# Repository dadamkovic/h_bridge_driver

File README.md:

The project is an implementation of an H-bridge driving IC DRV8702QRHBRQ1 that allows control of full H-bridge motor driver in different modes.
The ECU includes:
- buttons for manual control of the motor in both direction + braking
- Status LED
- ON/OFF switch
- Interface for banana plugs and probes
- Interface for electrical control

A chassis designed for 3D printing that protects the ECU. It is inteded to be printed from 3 pieces:
- 2x hard plastic shell (PLA, ABS, ...)
- 1x soft shell for protection against bumps (TPA)

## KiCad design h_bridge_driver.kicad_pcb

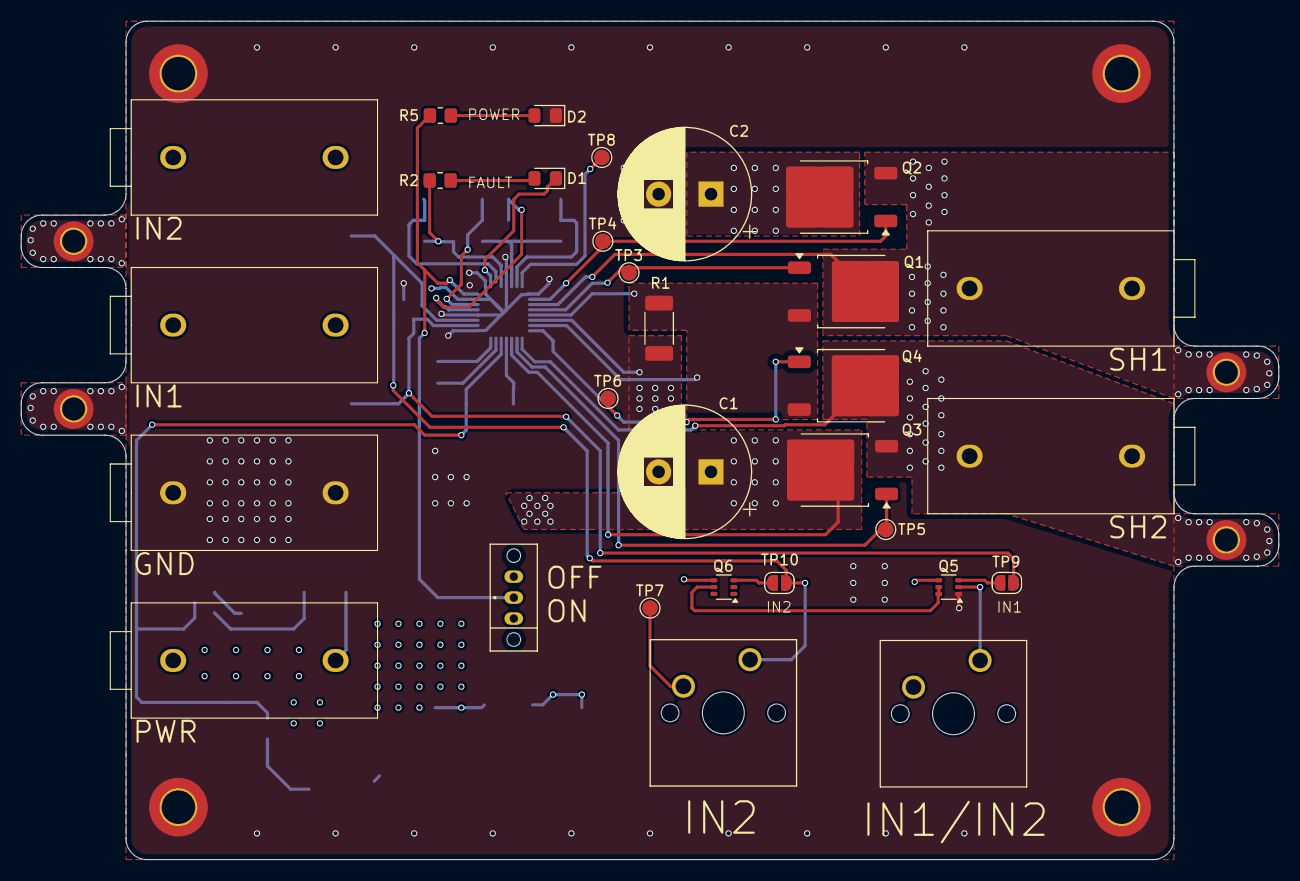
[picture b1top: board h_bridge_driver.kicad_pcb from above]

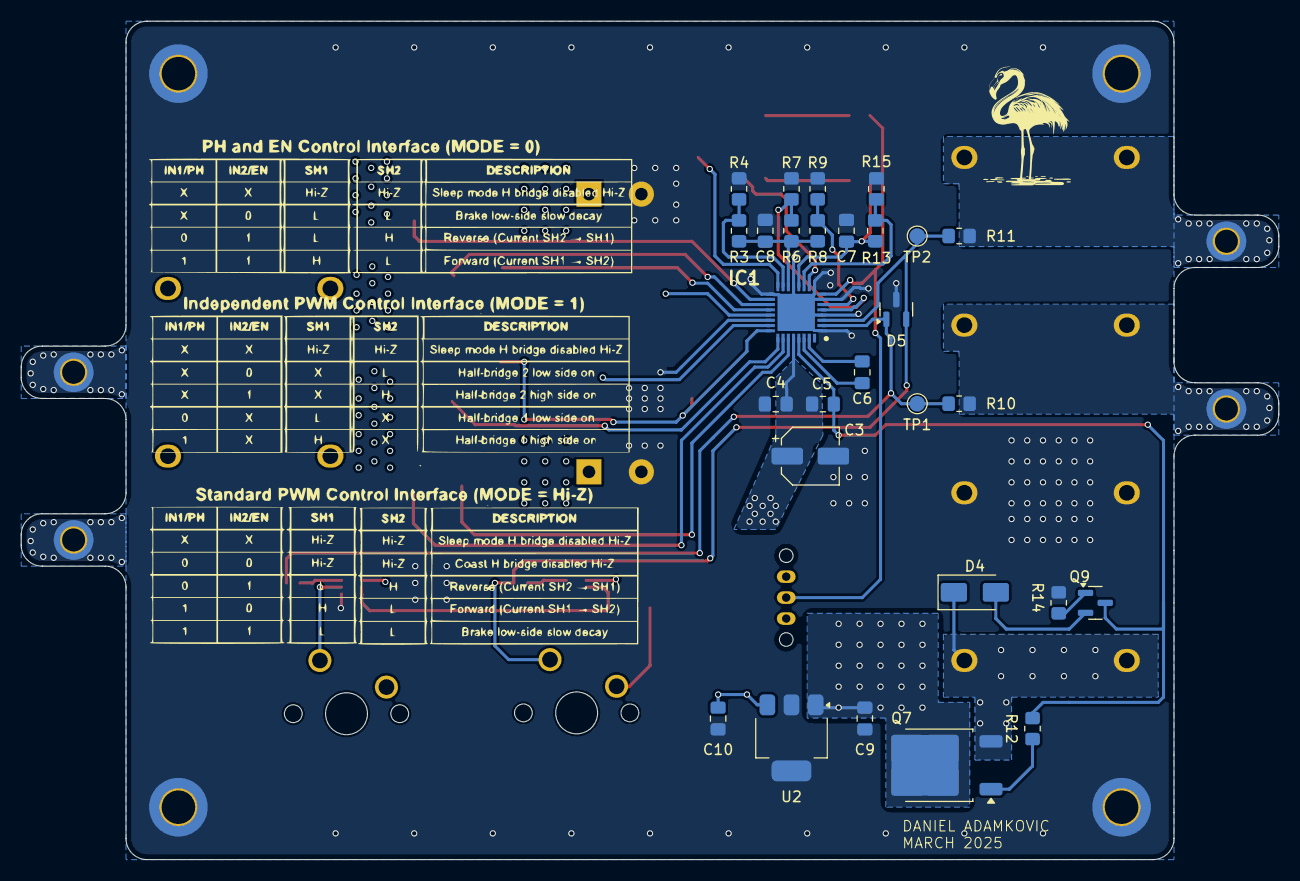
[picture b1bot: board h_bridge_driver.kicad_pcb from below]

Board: 4 copper layers, 120.0 x 80.0 mm, 66 parts (28 on the bottom side), 35 nets.

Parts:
C1, C2: 470u; CP_Radial_D12.5mm_P5.00mm
C3: 10u; CP_Elec_5x5.3
C4, C6: 0.1u; C_0805_2012Metric_Pad1.18x1.45mm_HandSolder
C5, C7, C8: 1u; C_0805_2012Metric_Pad1.18x1.45mm_HandSolder
C9, C10: 2.2u; C_0805_2012Metric_Pad1.18x1.45mm_HandSolder
D1: RED; LED_0805_2012Metric_Pad1.15x1.40mm_HandSolder
D2: GREEN; LED_0805_2012Metric_Pad1.15x1.40mm_HandSolder
D4: US1M; D_SMA
D5: 2BZX84Cxx; SOT-23
H1, H2, H3, H4: MountingHole_Pad; MountingHole_3.2mm_M3_DIN965_Pad_TopBottom
H5, H6, H7, H8: MountingHole_Pad; MountingHole_2.2mm_M2_DIN965_Pad_TopBottom
IC1: DRV8702QRHBRQ1; QFN50P500X500X90-33N-D
J1, J4, J5: IN1; BananaPlug-Aliexpress
J2: IN2; BananaPlug-Aliexpress
J3: SUPP; BananaPlug-Aliexpress
J6: GND; BananaPlug-Aliexpress
Q1, Q2, Q3, Q4, Q7: SUD80460E; TO-252-2
Q5, Q6: MUN5336DW1; SOT-363_SC-70-6
Q9: MMBTA42; SOT-23
R1: R_US; R_2010_5025Metric_Pad1.40x2.65mm_HandSolder
R2, R5: 500R; R_0805_2012Metric_Pad1.20x1.40mm_HandSolder
R3, R4, R6, R7, R8, R9, R13, R15: R_US; R_0805_2012Metric_Pad1.20x1.40mm_HandSolder
R10, R11: 100R; R_0805_2012Metric_Pad1.20x1.40mm_HandSolder
R12: 10k; R_0805_2012Metric_Pad1.20x1.40mm_HandSolder
R14: 43k; R_0805_2012Metric_Pad1.20x1.40mm_HandSolder
SW1: SW_DIP_x01; EG 1248
SW2, SW4: IN2; SW_Cherry_MX_1.00u_PCB
TP1, TP2, TP3, TP4, TP5, TP6, TP7, TP8: TestPoint; TestPoint_Pad_D1.5mm
TP9, TP10: TestPoint_2Pole; SolderJumper-2_P1.3mm_Open_RoundedPad1.0x1.5mm
U2: MCP1792x-5002xDB; SOT-223-3_TabPin2

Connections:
/5V_EXTERNAL: C10.1, Q5.4 (E1), Q6.4 (E1), SW1.1, SW2.2, SW4.2, TP7.1, U2.3 (VO)
/AVDD: C8.1, IC1.14 (AVDD), R3.1, R6.2, R8.2
/DVDD: C7.1, IC1.12 (DVDD), R2.2, R13.2
/GH1: IC1.18 (GH1), Q2.1 (G), TP4.1
/GH2: IC1.26 (GH2), Q3.1 (G), TP5.1
/GL1: IC1.20 (GL1), Q1.1 (G), TP3.1
/GL2: IC1.24 (GL2), Q4.1 (G), TP6.1
/IDRIVE: IC1.5 (IDRIVE), R6.1, R7.2
/IN1: D5.1 (K), IC1.2 (IN1/PH), R10.2, TP1.1, TP9.2
/IN2: D5.2 (K), IC1.3 (IN2/EN), R11.1, SW2.1, TP2.1, TP10.2
/MODE: IC1.11 (MODE), R13.1, R15.2
/SH1: H7.1, IC1.19 (SH1), J4.1, Q1.2 (D), Q2.3 (S)
/SH2: H8.1, IC1.25 (SH2), J5.1, Q3.3 (S), Q4.2 (D)
/SP: IC1.21 (SP), IC1.23 (SL2), Q1.3 (S), Q4.3 (S), R1.1
/VDS: IC1.6 (VDS), R8.1, R9.2
GND: C1.2, C2.2, C3.2, C4.2, C7.2, C8.2, C9.2, C10.2, D2.1 (K), D5.3 (A), H1.1, H2.1, H3.1, H4.1, IC1.1 (GND_1), IC1.4 (GND_2), IC1.7 (GND_3), IC1.9 (GND_4), IC1.13 (GND_5), IC1.17 (GND_6), IC1.22 (SN), IC1.33 (THERM_PAD), J6.1, Q5.1 (E2), R1.2, R4.2, R7.1, R9.1, R14.1, R15.1, U2.2 (GND)
unnamed: D1.2 (A), R2.1
unnamed: D1.1 (K), IC1.10 (NFAULT)
unnamed: D2.2 (A), R5.2
unnamed: D4.2 (A), Q9.2 (E)
unnamed: D4.1 (K), J3.1, Q7.3 (S)
unnamed: C6.1, IC1.30 (CPH)
unnamed: C6.2, IC1.31 (CPL)
unnamed: IC1.8 (NSLEEP), R5.1, SW1.2
unnamed: C5.2, IC1.29 (VCP), Q9.3 (C), R12.1
unnamed: C1.1, C2.1, C3.1, C4.1, C5.1, C9.1, IC1.27 (VDRAIN), IC1.28 (VM), Q2.2 (D), Q3.2 (D), Q7.2 (D), U2.1 (VI)
unnamed: IC1.15 (VREF), R3.2, R4.1
unnamed: H5.1, J1.1, R10.1
unnamed: H6.1, J2.1, R11.2
unnamed: Q5.5 (B1), Q5.6 (C2), Q6.5 (B1)
unnamed: Q5.3 (C1), TP9.1
unnamed: Q5.2 (B2), SW4.1
unnamed: Q6.3 (C1), TP10.1
unnamed: Q7.1 (G), R12.2
unnamed: Q9.1 (B), R14.2

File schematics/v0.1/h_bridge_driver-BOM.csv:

Reference,Value,Datasheet,Footprint,Qty,DNP,Source
"C1,C2",470u,~,Capacitor_THT:CP_Radial_D12.5mm_P5.00mm,2,,https://www.mouser.com/ProductDetail/Nichicon/UVR1J471MHD?qs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
C3,10u,~,Capacitor_SMD:CP_Elec_5x5.3,1,,https://www.mouser.com/ProductDetail/Wurth-Elektronik/865080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
"C4,C6",0.1u,~,Capacitor_SMD:C_0805_2012Metric_Pad1.18x1.45mm_HandSolder,2,,https://www.mouser.com/ProductDetail/KEMET/C0805C104M5RACTU?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
"C5,C7,C8",1u,~,Capacitor_SMD:C_0805_2012Metric_Pad1.18x1.45mm_HandSolder,3,,https://www.mouser.com/ProductDetail/Samsung-Electro-Mechani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
"C9,C10",2.2u,~,Capacitor_SMD:C_0805_2012Metric_Pad1.18x1.45mm_HandSolder,2,,https://www.mouser.com/ProductDetail/TAIYO-YUDEN/UMK212ABJ22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
D1,RED,~,LED_SMD:LED_0805_2012Metric_Pad1.15x1.40mm_HandSolder,1,,https://www.mouser.com/ProductDetail/Lite-On/LTST-C171EKT?qs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
D2,GREEN,~,LED_SMD:LED_0805_2012Metric_Pad1.15x1.40mm_HandSolder,1,,https://www.mouser.com/ProductDetail/Lite-On/LTST-S220GKT?qs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
D4,US1M,https://www.diodes.com/assets/Datasheets/ds16008.pdf,Diode_SMD:D_SMA,1,,https://www.mouser.com/ProductDetail/Comchip-Technology/US1M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
D5,2BZX84Cxx,https://diotec.com/tl_files/diotec/files/pdf/datasheets/bzx8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,Package_TO_SOT_SMD:SOT-23,1,,https://www.mouser.com/ProductDetail/Diotec-Semiconductor/2B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
IC1,DRV8702QRHBRQ1,http://www.ti.com/lit/gpn/drv8702-q1,User_HBridgeDriver:QFN50P500X500X90-33N-D,1,,https://www.mouser.com/ProductDetail/Texas-Instruments/DRV87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
"J1,J4,J5",IN1,~,User_BananaTerminal:BananaPlug-Aliexpress,3,,
"J2,SW2,SW4",IN2,~,-- mixed values --,3,,
J3,SUPP,~,User_BananaTerminal:BananaPlug-Aliexpress,1,,
J6,GND,~,User_BananaTerminal:BananaPlug-Aliexpress,1,,
"Q1,Q2,Q3,Q4,Q7",SUD80460E,https://www.vishay.com/docs/76248/sud80460e.pdf,Package_TO_SOT_SMD:TO-252-2,5,,https://www.mouser.com/ProductDetail/Vishay-Siliconix/SUD804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
"Q5,Q6",MUN5336DW1,https://www.onsemi.com/download/data-sheet/pdf/dtc115ep-d.pdf,Package_TO_SOT_SMD:SOT-363_SC-70-6,2,,
Q9,MMBTA42,https://www.onsemi.com/pub/Collateral/MMBTA42LT1-D.PDF,Package_TO_SOT_SMD:SOT-23,1,,https://www.mouser.com/ProductDetail/Diodes-Incorporated/MMB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
"R1,R3,R4,R6,R7,R8,R9,R13,R15",R_US,~,-- mixed values --,9,,
"R2,R5",500R,~,Resistor_SMD:R_0805_2012Metric_Pad1.20x1.40mm_HandSolder,2,,
"R10,R11",100R,~,Resistor_SMD:R_0805_2012Metric_Pad1.20x1.40mm_HandSolder,2,,
R12,10k,~,Resistor_SMD:R_0805_2012Metric_Pad1.20x1.40mm_HandSolder,1,,
R14,43k,~,Resistor_SMD:R_0805_2012Metric_Pad1.20x1.40mm_HandSolder,1,,
SW1,SW_DIP_x01,~,User_SliderSwitch:EG 1248,1,,
"TP1,TP2,TP3,TP4,TP5,TP6,TP7,TP8",TestPoint,~,TestPoint:TestPoint_Pad_D1.5mm,8,,
"TP9,TP10",TestPoint_2Pole,~,Jumper:SolderJumper-2_P1.3mm_Open_RoundedPad1.0x1.5mm,2,,
U2,MCP1792x-5002xDB,https://ww1.microchip.com/downloads/aemDocuments/documents/A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,Package_TO_SOT_SMD:SOT-223-3_TabPin2,1,,https://www.mouser.com/ProductDetail/Microchip-Technology/MC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

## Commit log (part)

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2025-03-29 First manufactured version of h-bridge-driver
2025-03-30 Fixed incorrect plane dimensions on power layer. Fixed wrong connection of BJT to RVP MOSFET gate.
